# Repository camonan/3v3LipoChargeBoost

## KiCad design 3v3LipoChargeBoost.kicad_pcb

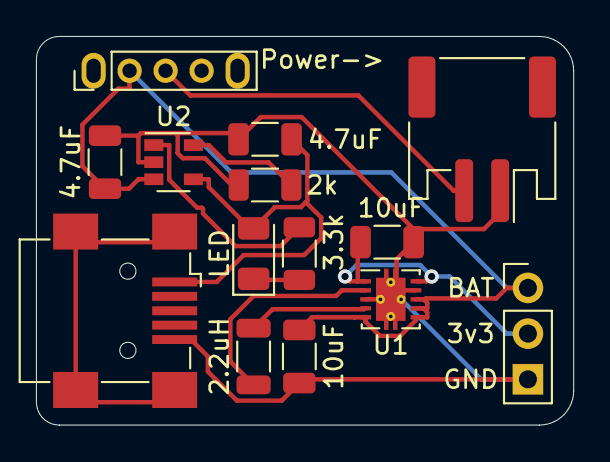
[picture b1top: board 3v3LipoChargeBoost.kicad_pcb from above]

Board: 2 copper layers, 29.8 x 21.6 mm, 14 parts (0 on the bottom side), 10 nets.

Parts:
C1, C2: 10uF; C_1206_3216Metric
C3, C4: 4.7uF; C_1206_3216Metric
D1: LED; LED_1206_3216Metric
J1: BATT; JST_PH_S2B-PH-SM4-TB_1x02-1MP_P2.00mm_Horizontal
J2: USB_B_Mini; USB_Mini-B_Wuerth_65100516121_Horizontal
J3: Output; PinHeader_1x03_P2.54mm_Vertical
L1: 2.2uH; L_1206_3216Metric
R1: 3.3k; R_1206_3216Metric
R2: 2k; R_1206_3216Metric
SW1: Power->; 3pin_switch
U1: TPS63001; Texas_DRC0010J_ThermalVias
U2: MCP73831-2-OT; SOT-23-5

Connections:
+3V3: C2.1, J3.2, U1.1, U1.10
BATT: C1.1, C4.1, J3.1, SW1.2, U1.5, U1.6, U1.7, U1.8, U2.3
GND: C1.2, C2.2, C3.2, C4.2, J1.1, J2.5, J3.3, R2.1, U1.3, U1.9, U1.11, U2.2
unnamed: C3.1, D1.2, J2.1, U2.4
unnamed: D1.1, R1.2
unnamed: J1.2, SW1.1
unnamed: L1.1, U1.4
unnamed: L1.2, U1.2
unnamed: R1.1, U2.1
unnamed: R2.2, U2.5
